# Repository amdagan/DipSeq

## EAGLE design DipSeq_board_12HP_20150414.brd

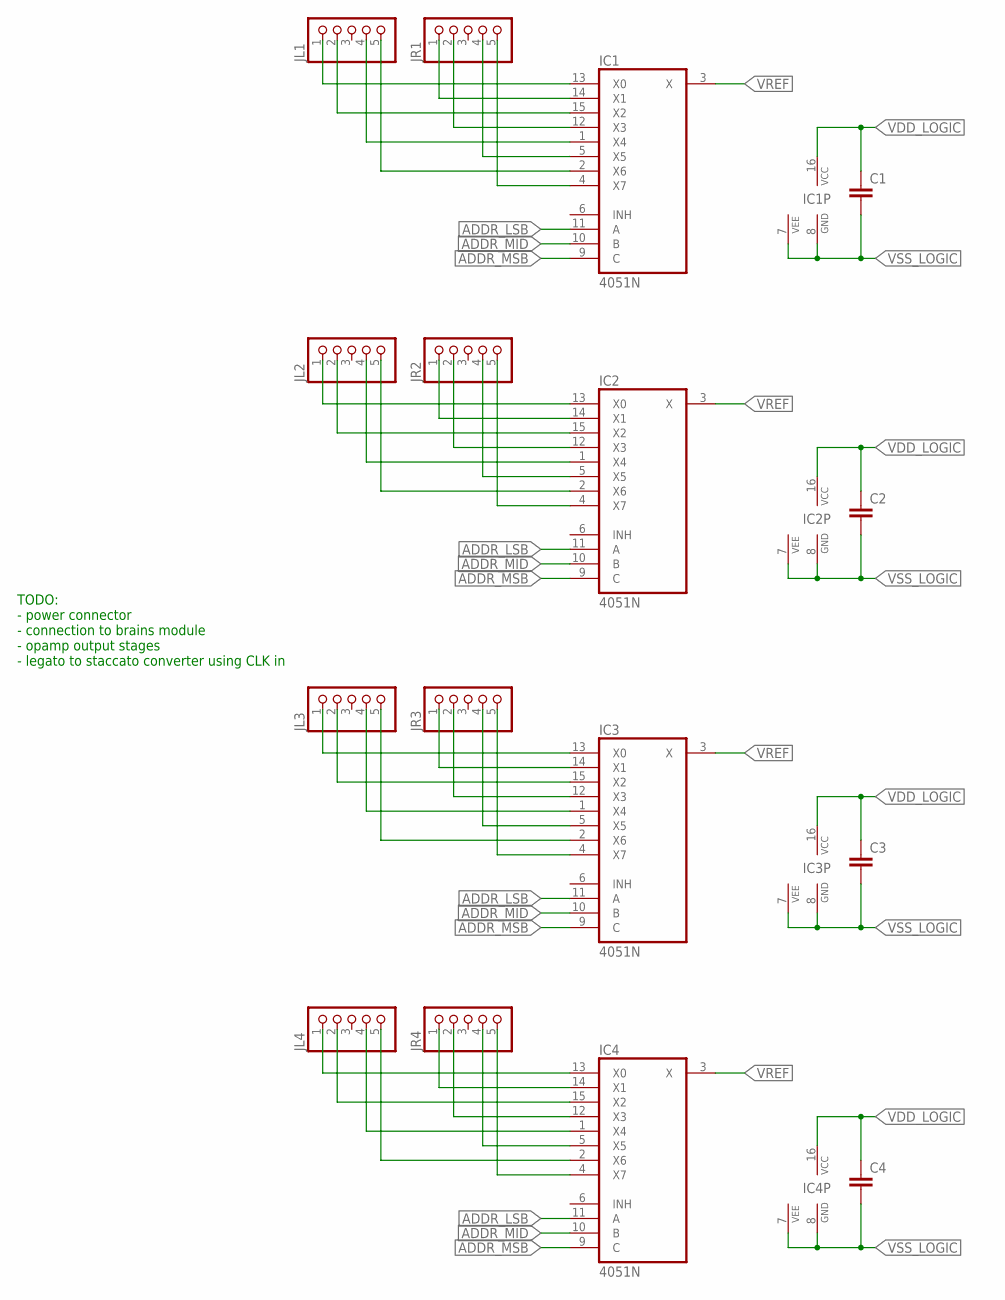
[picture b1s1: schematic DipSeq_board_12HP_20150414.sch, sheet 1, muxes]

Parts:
C1, C2, C3, C4: C-EU; CAP_0805
IC1, IC2, IC3, IC4: 4051N; DIL16
JL1, JL2, JL3, JL4: PINHD-1X5; 1X05
JR1, JR2, JR3, JR4: PINHD-1X5; 1X05

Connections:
ADDR_LSB: IC1.11 (A), IC2.11 (A), IC3.11 (A), IC4.11 (A)
ADDR_MID: IC1.10 (B), IC2.10 (B), IC3.10 (B), IC4.10 (B)
ADDR_MSB: IC1.9 (C), IC2.9 (C), IC3.9 (C), IC4.9 (C)
S1: IC1.13 (X0), JL1.1
S2: IC1.14 (X1), JR1.1
S3: IC1.15 (X2), JL1.2
S4: IC1.12 (X3), JR1.2
S5: IC1.1 (X4), JL1.4
S6: IC1.5 (X5), JR1.4
S7: IC1.2 (X6), JL1.5
S8: IC1.4 (X7), JR1.5
S9: IC2.13 (X0), JL2.1
S10: IC2.15 (X2), JL2.2
S11: IC2.1 (X4), JL2.4
S12: IC2.2 (X6), JL2.5
S13: IC2.14 (X1), JR2.1
S14: IC2.12 (X3), JR2.2
S15: IC2.5 (X5), JR2.4
S16: IC2.4 (X7), JR2.5
S17: IC3.13 (X0), JL3.1
S18: IC3.15 (X2), JL3.2
S19: IC3.1 (X4), JL3.4
S20: IC3.2 (X6), JL3.5
S21: IC3.14 (X1), JR3.1
S22: IC3.12 (X3), JR3.2
S23: IC3.5 (X5), JR3.4
S24: IC3.4 (X7), JR3.5
S25: IC4.13 (X0), JL4.1
S26: IC4.15 (X2), JL4.2
S27: IC4.1 (X4), JL4.4
S28: IC4.2 (X6), JL4.5
S29: IC4.14 (X1), JR4.1
S30: IC4.12 (X3), JR4.2
S31: IC4.5 (X5), JR4.4
S32: IC4.4 (X7), JR4.5
VDD_LOGIC: C1.1, C2.1, C3.1, C4.1, IC1.16 (VCC), IC2.16 (VCC), IC3.16 (VCC), IC4.16 (VCC)
VREF: IC1.3 (X), IC2.3 (X), IC3.3 (X), IC4.3 (X)
VSS_LOGIC: C1.2, C2.2, C3.2, C4.2, IC1.7 (VEE), IC1.8 (GND), IC2.7 (VEE), IC2.8 (GND), IC3.7 (VEE), IC3.8 (GND), IC4.7 (VEE), IC4.8 (GND)

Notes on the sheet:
TODO: - power connector - connection to brains module - opamp output stages - legato to staccato converter using CLK in

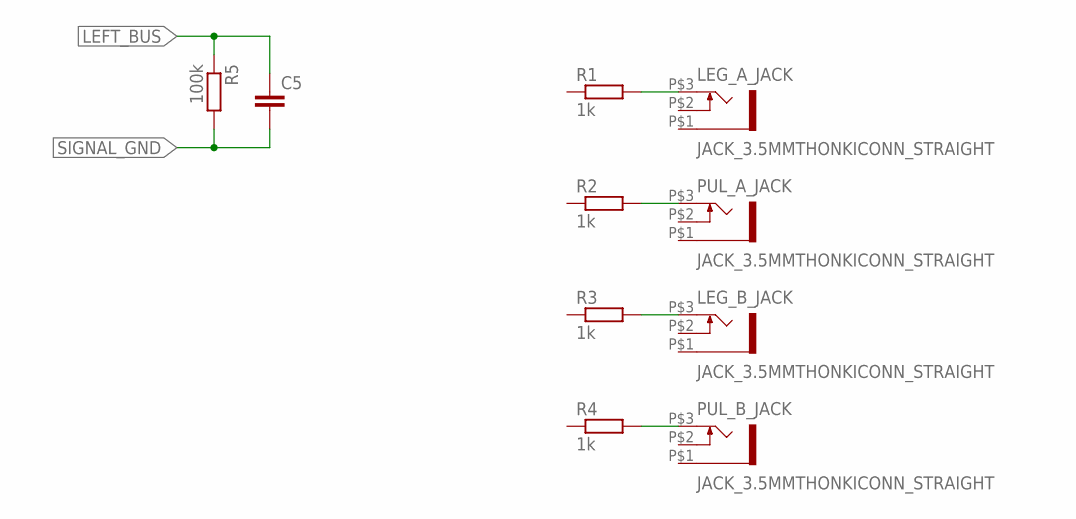
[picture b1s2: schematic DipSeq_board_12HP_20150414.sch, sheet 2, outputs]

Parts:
C5: C-EU; CAP_0805
LEG_A_JACK: JACK_3.5MMTHONKICONN_STRAIGHT; THONKICONN_LAYOUT
LEG_B_JACK: JACK_3.5MMTHONKICONN_STRAIGHT; THONKICONN_LAYOUT
PUL_A_JACK: JACK_3.5MMTHONKICONN_STRAIGHT; THONKICONN_LAYOUT
PUL_B_JACK: JACK_3.5MMTHONKICONN_STRAIGHT; THONKICONN_LAYOUT
R1, R2, R3, R4: 1k; R_0805_MINE
R5: 100k; R_0805_MINE

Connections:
LEFT_BUS: C5.1, R5.1
unnamed: LEG_A_JACK.P$3 (TIP), R1.2
unnamed: PUL_A_JACK.P$3 (TIP), R2.2
unnamed: LEG_B_JACK.P$3 (TIP), R3.2
unnamed: PUL_B_JACK.P$3 (TIP), R4.2
SIGNAL_GND: C5.2, R5.2

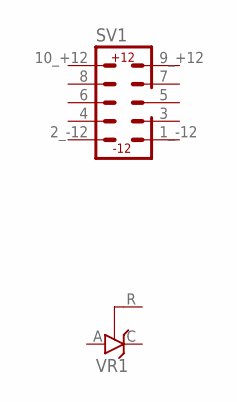
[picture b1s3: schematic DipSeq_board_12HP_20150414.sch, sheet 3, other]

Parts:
SV1: BOXHEADER_10P; MY_BOXHEADER_2X5
VR1: TL431CLP; TO92-CLP

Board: 2 copper layers, 28 parts (9 on the bottom side), 44 nets, no tracks yet.

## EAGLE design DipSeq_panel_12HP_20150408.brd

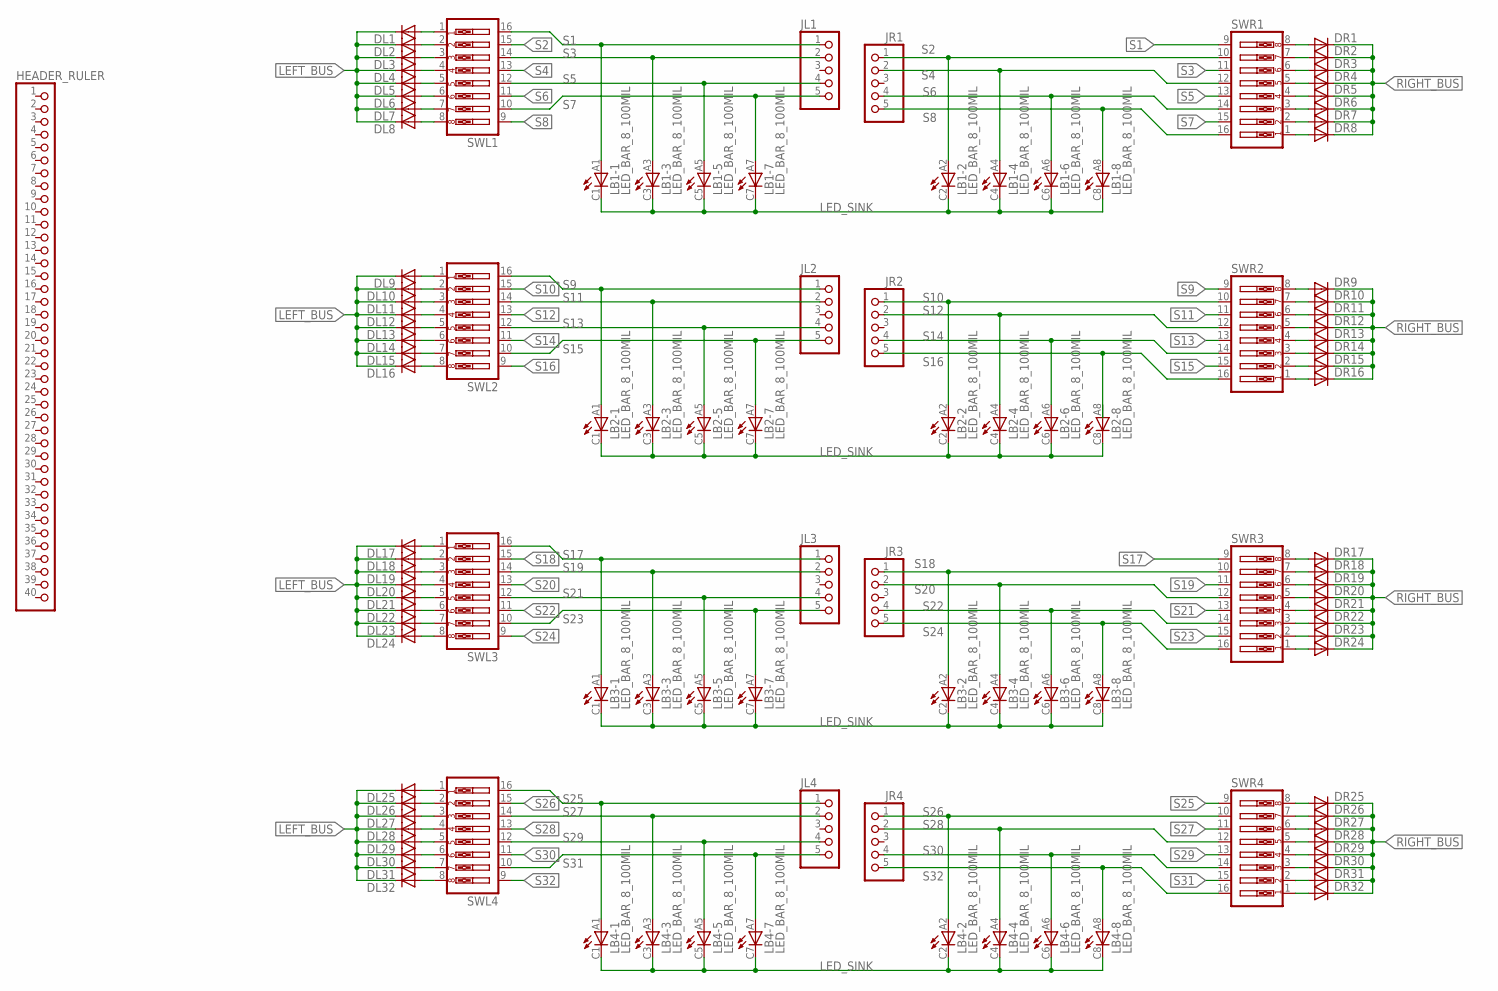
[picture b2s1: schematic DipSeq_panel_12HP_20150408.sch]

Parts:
DL1, DL2, DL3, DL4, DL5, DL6, DL7, DL8, DL9, DL10, DL11, DL12, DL13, DL14, DL15, DL16, DL17, DL18, DL19, DL20, DL21, DL22, DL23, DL24, DL25, DL26, DL27, DL28, DL29, DL30, DL31, DL32: DIODE-SOD323-W; SOD323-W
DR1, DR2, DR3, DR4, DR5, DR6, DR7, DR8, DR9, DR10, DR11, DR12, DR13, DR14, DR15, DR16, DR17, DR18, DR19, DR20, DR21, DR22, DR23, DR24, DR25, DR26, DR27, DR28, DR29, DR30, DR31, DR32: DIODE-SOD323-W; SOD323-W
HEADER_RULER: PINHD-1X40; 1X40
JL1, JL2, JL3, JL4: PINHD-1X5; 1X05
JR1, JR2, JR3, JR4: PINHD-1X5; 1X05
LB1, LB2, LB3, LB4: LED_BAR_8_100MIL; LED_BAR_8
SWL1, SWL2, SWL3, SWL4: SW_DIP-8PIANO_STYLE; PIANO_DIPSWITCH_08
SWR1, SWR2, SWR3, SWR4: SW_DIP-8PIANO_STYLE; PIANO_DIPSWITCH_08

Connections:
LED_SINK: LB1.C1 (C), LB1.C2 (C), LB1.C3 (C), LB1.C4 (C), LB1.C5 (C), LB1.C6 (C), LB1.C7 (C), LB1.C8 (C), LB2.C1 (C), LB2.C2 (C), LB2.C3 (C), LB2.C4 (C), LB2.C5 (C), LB2.C6 (C), LB2.C7 (C), LB2.C8 (C), LB3.C1 (C), LB3.C2 (C), LB3.C3 (C), LB3.C4 (C), LB3.C5 (C), LB3.C6 (C), LB3.C7 (C), LB3.C8 (C), LB4.C1 (C), LB4.C2 (C), LB4.C3 (C), LB4.C4 (C), LB4.C5 (C), LB4.C6 (C), LB4.C7 (C), LB4.C8 (C)
LEFT_BUS: DL1.C, DL2.C, DL3.C, DL4.C, DL5.C, DL6.C, DL7.C, DL8.C, DL9.C, DL10.C, DL11.C, DL12.C, DL13.C, DL14.C, DL15.C, DL16.C, DL17.C, DL18.C, DL19.C, DL20.C, DL21.C, DL22.C, DL23.C, DL24.C, DL25.C, DL26.C, DL27.C, DL28.C, DL29.C, DL30.C, DL31.C, DL32.C
unnamed: DL1.A, SWL1.1
unnamed: DL2.A, SWL1.2
unnamed: DL3.A, SWL1.3
unnamed: DL4.A, SWL1.4
unnamed: DL5.A, SWL1.5
unnamed: DL6.A, SWL1.6
unnamed: DL7.A, SWL1.7
unnamed: DL8.A, SWL1.8
unnamed: DR1.A, SWR1.8
unnamed: DR2.A, SWR1.7
unnamed: DR3.A, SWR1.6
unnamed: DR8.A, SWR1.1
unnamed: DR7.A, SWR1.2
unnamed: DR6.A, SWR1.3
unnamed: DR5.A, SWR1.4
unnamed: DR4.A, SWR1.5
unnamed: DL9.A, SWL2.1
unnamed: DL10.A, SWL2.2
unnamed: DL11.A, SWL2.3
unnamed: DL12.A, SWL2.4
unnamed: DL15.A, SWL2.7
unnamed: DL16.A, SWL2.8
unnamed: DR9.A, SWR2.8
unnamed: DR10.A, SWR2.7
unnamed: DR11.A, SWR2.6
unnamed: DR16.A, SWR2.1
unnamed: DR15.A, SWR2.2
unnamed: DR14.A, SWR2.3
unnamed: DR13.A, SWR2.4
unnamed: DR12.A, SWR2.5
unnamed: DL13.A, SWL2.5
unnamed: DL14.A, SWL2.6
unnamed: DL17.A, SWL3.1
unnamed: DL18.A, SWL3.2
unnamed: DL19.A, SWL3.3
unnamed: DL20.A, SWL3.4
unnamed: DL23.A, SWL3.7
unnamed: DL24.A, SWL3.8
unnamed: DR17.A, SWR3.8
unnamed: DR18.A, SWR3.7
unnamed: DR19.A, SWR3.6
unnamed: DR24.A, SWR3.1
unnamed: DR23.A, SWR3.2
unnamed: DR22.A, SWR3.3
unnamed: DR21.A, SWR3.4
unnamed: DR20.A, SWR3.5
unnamed: DL21.A, SWL3.5
unnamed: DL22.A, SWL3.6
unnamed: DL25.A, SWL4.1
unnamed: DL26.A, SWL4.2
unnamed: DL27.A, SWL4.3
unnamed: DL28.A, SWL4.4
unnamed: DL31.A, SWL4.7
unnamed: DL32.A, SWL4.8
unnamed: DR25.A, SWR4.8
unnamed: DR26.A, SWR4.7
unnamed: DR27.A, SWR4.6
unnamed: DR32.A, SWR4.1
unnamed: DR31.A, SWR4.2
unnamed: DR30.A, SWR4.3
unnamed: DR29.A, SWR4.4
unnamed: DR28.A, SWR4.5
unnamed: DL29.A, SWL4.5
unnamed: DL30.A, SWL4.6
RIGHT_BUS: DR1.C, DR2.C, DR3.C, DR4.C, DR5.C, DR6.C, DR7.C, DR8.C, DR9.C, DR10.C, DR11.C, DR12.C, DR13.C, DR14.C, DR15.C, DR16.C, DR17.C, DR18.C, DR19.C, DR20.C, DR21.C, DR22.C, DR23.C, DR24.C, DR25.C, DR26.C, DR27.C, DR28.C, DR29.C, DR30.C, DR31.C, DR32.C
S1: JL1.1, LB1.A1 (A), SWL1.16, SWR1.9
S2: JR1.1, LB1.A2 (A), SWL1.15, SWR1.10
S3: JL1.2, LB1.A3 (A), SWL1.14, SWR1.11
S4: JR1.2, LB1.A4 (A), SWL1.13, SWR1.12
S5: JL1.4, LB1.A5 (A), SWL1.12, SWR1.13
S6: JR1.4, LB1.A6 (A), SWL1.11, SWR1.14
S7: JL1.5, LB1.A7 (A), SWL1.10, SWR1.15
S8: JR1.5, LB1.A8 (A), SWL1.9, SWR1.16
S9: JL2.1, LB2.A1 (A), SWL2.16, SWR2.9
S10: JR2.1, LB2.A2 (A), SWL2.15, SWR2.10
S11: JL2.2, LB2.A3 (A), SWL2.14, SWR2.11
S12: JR2.2, LB2.A4 (A), SWL2.13, SWR2.12
S13: JL2.4, LB2.A5 (A), SWL2.12, SWR2.13
S14: JR2.4, LB2.A6 (A), SWL2.11, SWR2.14
S15: JL2.5, LB2.A7 (A), SWL2.10, SWR2.15
S16: JR2.5, SWL2.9, SWR2.16
S17: JL3.1, LB3.A1 (A), SWL3.16, SWR3.9
S18: JR3.1, LB3.A2 (A), SWL3.15, SWR3.10
S19: JL3.2, LB3.A3 (A), SWL3.14, SWR3.11
S20: JR3.2, LB3.A4 (A), SWL3.13, SWR3.12
S21: JL3.4, LB3.A5 (A), SWL3.12, SWR3.13
S22: JR3.4, LB3.A6 (A), SWL3.11, SWR3.14
S23: JL3.5, LB3.A7 (A), SWL3.10, SWR3.15
S24: JR3.5, LB3.A8 (A), SWL3.9, SWR3.16
S25: JL4.1, LB4.A1 (A), SWL4.16, SWR4.9
S26: JR4.1, LB4.A2 (A), SWL4.15, SWR4.10
S27: JL4.2, LB4.A3 (A), SWL4.14, SWR4.11
S28: JR4.2, LB4.A4 (A), SWL4.13, SWR4.12
S29: JL4.4, LB4.A5 (A), SWL4.12, SWR4.13
S30: JR4.4, LB4.A6 (A), SWL4.11, SWR4.14
S31: JL4.5, LB4.A7 (A), SWL4.10, SWR4.15
S32: JR4.5, LB4.A8 (A), SWL4.9, SWR4.16

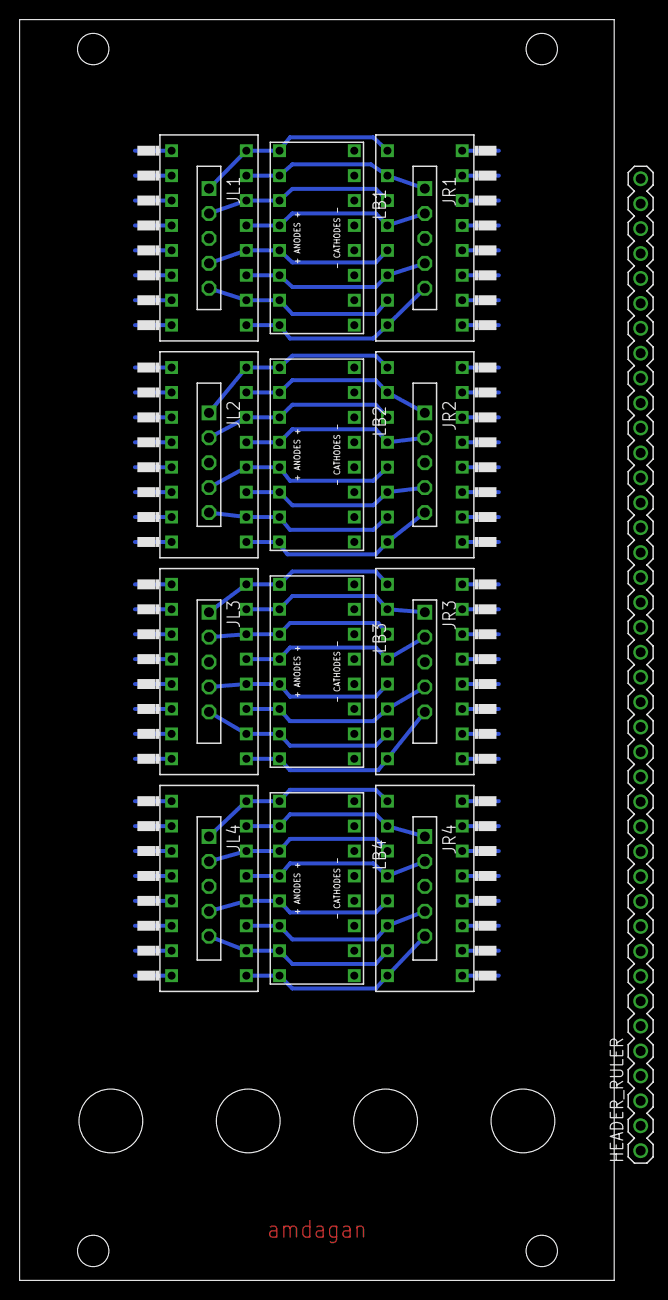
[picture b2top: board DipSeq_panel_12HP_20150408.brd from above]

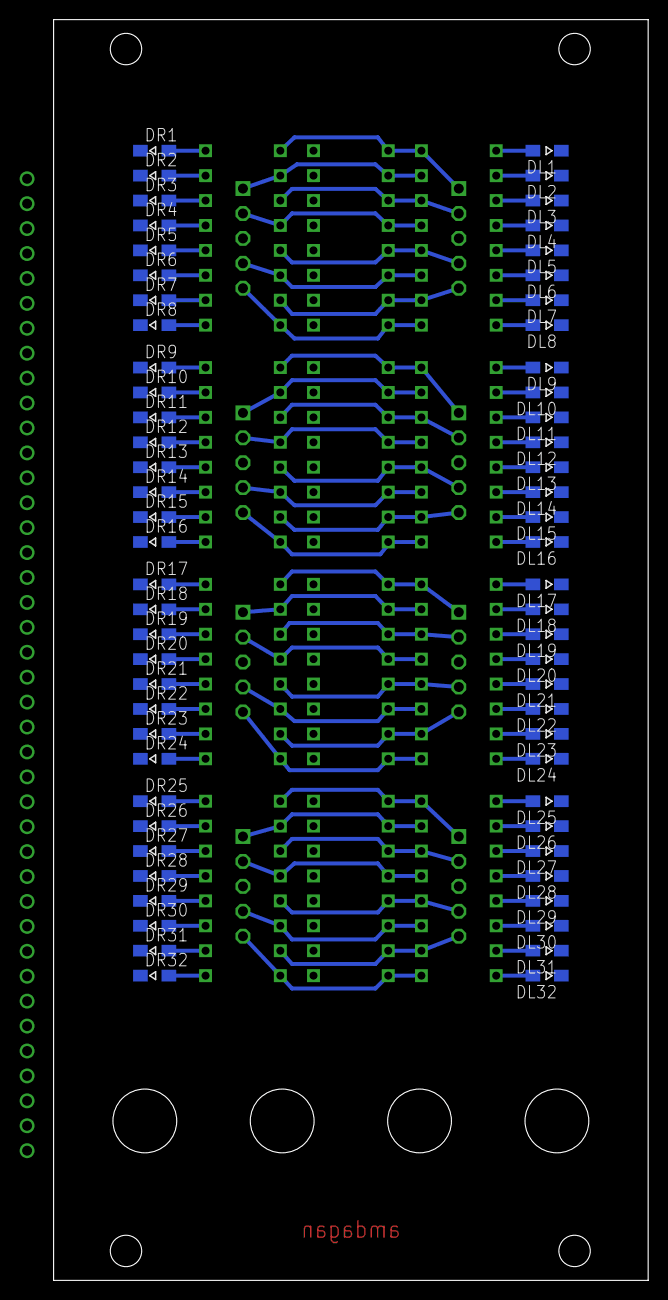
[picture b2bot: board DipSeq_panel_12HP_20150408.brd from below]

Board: 2 copper layers, 60.6 x 128.5 mm, 89 parts (64 on the bottom side), 99 nets.

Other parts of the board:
LEG_A: JACK_PANEL
LEG_B: JACK_PANEL
PUL_A: JACK_PANEL
PUL_B: JACK_PANEL

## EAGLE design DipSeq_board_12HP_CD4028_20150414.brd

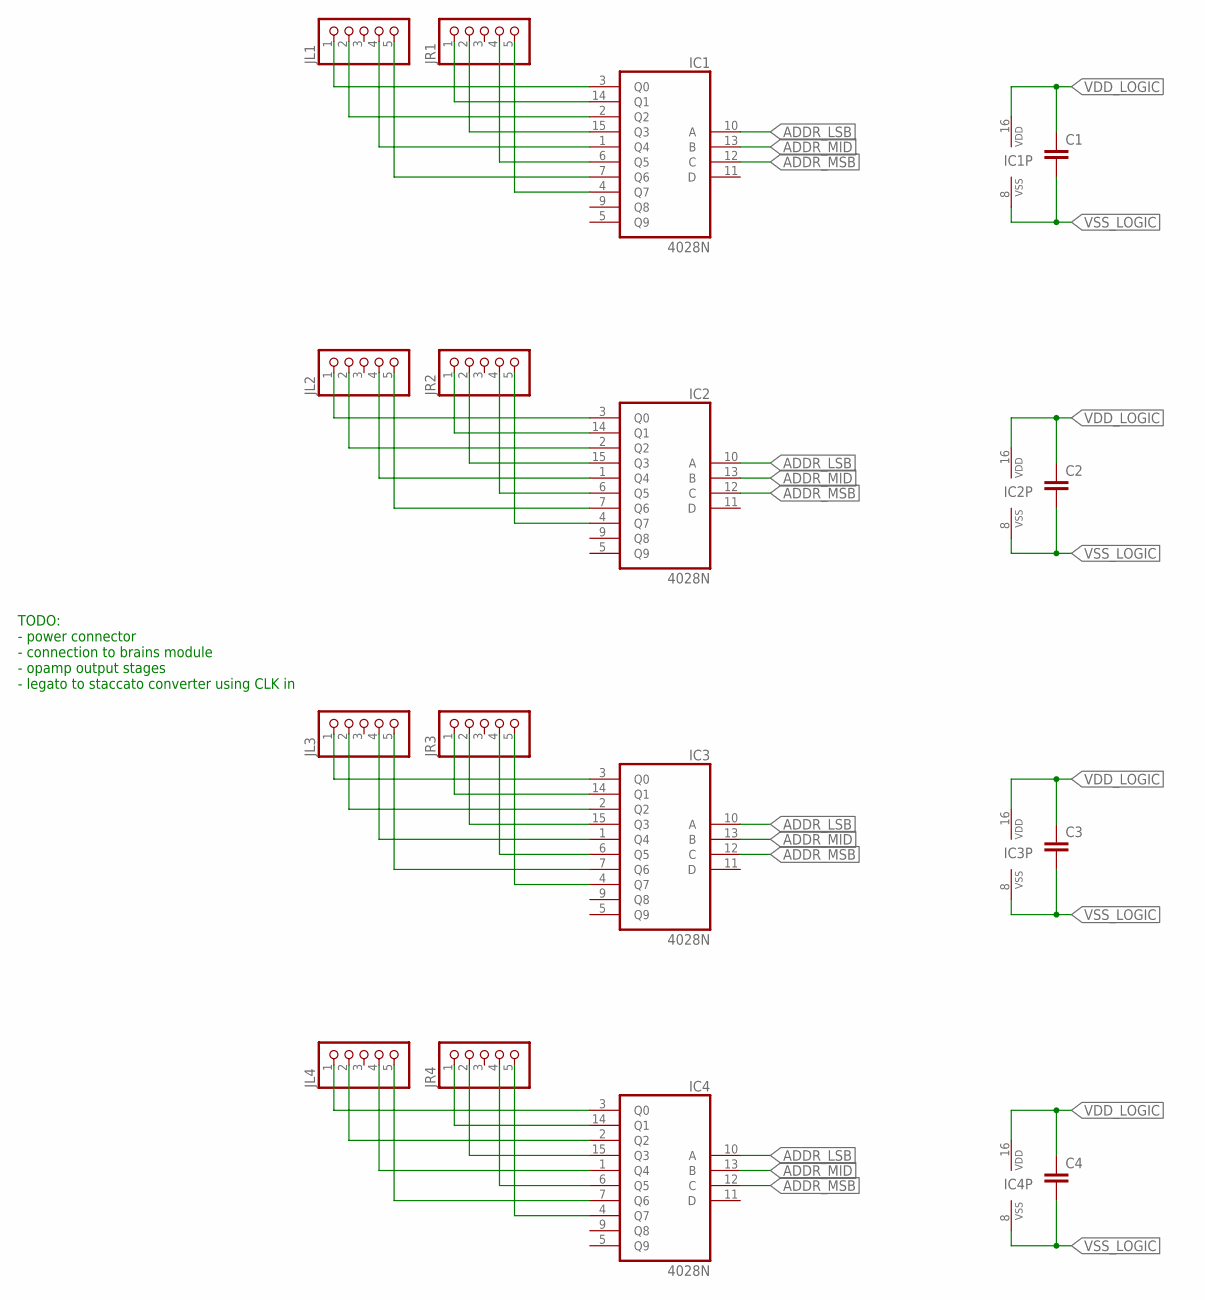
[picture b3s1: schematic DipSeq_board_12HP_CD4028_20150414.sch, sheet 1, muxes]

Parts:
C1, C2, C3, C4: C-EU; CAP_0805
IC1, IC2, IC3, IC4: 4028N; DIL16
JL1, JL2, JL3, JL4: PINHD-1X5; 1X05
JR1, JR2, JR3, JR4: PINHD-1X5; 1X05

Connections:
ADDR_LSB: IC2.10 (A), IC3.10 (A), IC4.10 (A)
ADDR_MID: IC2.13 (B), IC3.13 (B), IC4.13 (B)
ADDR_MSB: IC2.12 (C), IC3.12 (C), IC4.12 (C)
S1: IC1.3 (Q0), JL1.1
S2: IC1.14 (Q1), JR1.1
S3: IC1.2 (Q2), JL1.2
S4: IC1.15 (Q3), JR1.2
S5: IC1.1 (Q4), JL1.4
S6: IC1.6 (Q5), JR1.4
S7: IC1.7 (Q6), JL1.5
S8: IC1.4 (Q7), JR1.5
S9: IC2.3 (Q0), JL2.1
S10: IC2.2 (Q2), JL2.2
S11: IC2.1 (Q4), JL2.4
S12: IC2.7 (Q6), JL2.5
S13: IC2.14 (Q1), JR2.1
S14: IC2.15 (Q3), JR2.2
S15: IC2.6 (Q5), JR2.4
S16: IC2.4 (Q7), JR2.5
S17: IC3.3 (Q0), JL3.1
S18: IC3.2 (Q2), JL3.2
S19: IC3.1 (Q4), JL3.4
S20: IC3.7 (Q6), JL3.5
S21: IC3.14 (Q1), JR3.1
S22: IC3.15 (Q3), JR3.2
S23: IC3.6 (Q5), JR3.4
S24: IC3.4 (Q7), JR3.5
S25: IC4.3 (Q0), JL4.1
S26: IC4.2 (Q2), JL4.2
S27: IC4.1 (Q4), JL4.4
S28: IC4.7 (Q6), JL4.5
S29: IC4.14 (Q1), JR4.1
S30: IC4.15 (Q3), JR4.2
S31: IC4.6 (Q5), JR4.4
S32: IC4.4 (Q7), JR4.5
VDD_LOGIC: C1.1, C2.1, C3.1, C4.1, IC1.16 (VDD), IC2.16 (VDD), IC3.16 (VDD), IC4.16 (VDD)
VSS_LOGIC: C1.2, C2.2, C3.2, C4.2, IC1.8 (VSS), IC2.8 (VSS), IC3.8 (VSS), IC4.8 (VSS)

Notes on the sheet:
TODO: - power connector - connection to brains module - opamp output stages - legato to staccato converter using CLK in

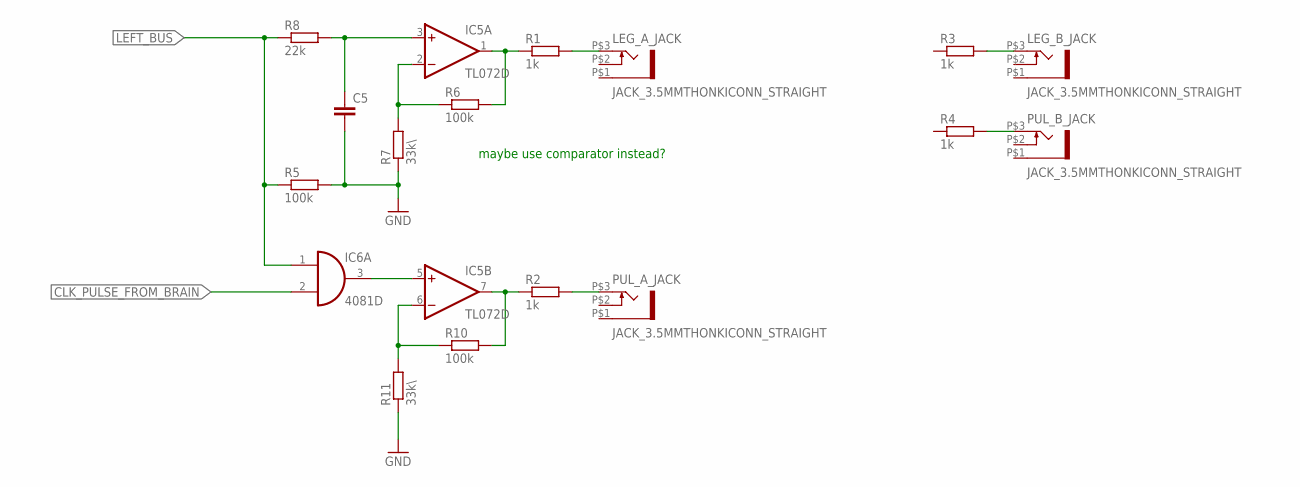
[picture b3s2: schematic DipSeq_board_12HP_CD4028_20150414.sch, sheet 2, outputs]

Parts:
C5: C-EU; CAP_0805
IC5: TL072D; SO08
IC6: 4081D; SO14
LEG_A_JACK: JACK_3.5MMTHONKICONN_STRAIGHT; THONKICONN_LAYOUT
LEG_B_JACK: JACK_3.5MMTHONKICONN_STRAIGHT; THONKICONN_LAYOUT
PUL_A_JACK: JACK_3.5MMTHONKICONN_STRAIGHT; THONKICONN_LAYOUT
PUL_B_JACK: JACK_3.5MMTHONKICONN_STRAIGHT; THONKICONN_LAYOUT
R1, R2, R3, R4: 1k; R_0805_MINE
R5, R6, R10: 100k; R_0805_MINE
R7, R11: 33k\; R_0805_MINE
R8: 22k; R_0805_MINE

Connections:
CLK_PULSE_FROM_BRAIN: IC6.2 (I1)
GND: C5.2, R5.2, R7.1, R11.1
LEFT_BUS: IC6.1 (I0), R5.1, R8.1
unnamed: LEG_A_JACK.P$3 (TIP), R1.2
unnamed: PUL_A_JACK.P$3 (TIP), R2.2
unnamed: LEG_B_JACK.P$3 (TIP), R3.2
unnamed: PUL_B_JACK.P$3 (TIP), R4.2
unnamed: IC5.1 (OUT), R1.1, R6.2
unnamed: IC5.2 (-IN), R6.1, R7.2
unnamed: C5.1, IC5.3 (+IN), R8.2
unnamed: IC5.7 (OUT), R2.1, R10.2
unnamed: IC5.6 (-IN), R10.1, R11.2
unnamed: IC5.5 (+IN), IC6.3 (O)
V+: IC5.8 (V+)
V-: IC5.4 (V-)
VDD: IC6.14 (VDD)
VSS: IC6.7 (VSS)

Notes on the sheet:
maybe use comparator instead?

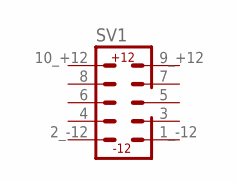
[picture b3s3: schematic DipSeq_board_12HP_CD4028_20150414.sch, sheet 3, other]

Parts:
SV1: BOXHEADER_10P; MY_BOXHEADER_2X5

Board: 2 copper layers, 34 parts (5 on the bottom side), 49 nets, no tracks yet.

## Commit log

2015-05-13 :lollipop: Added .gitattributes
2015-05-13 DipSeq
    Eurorack synth sequencer module based on DIP switches
